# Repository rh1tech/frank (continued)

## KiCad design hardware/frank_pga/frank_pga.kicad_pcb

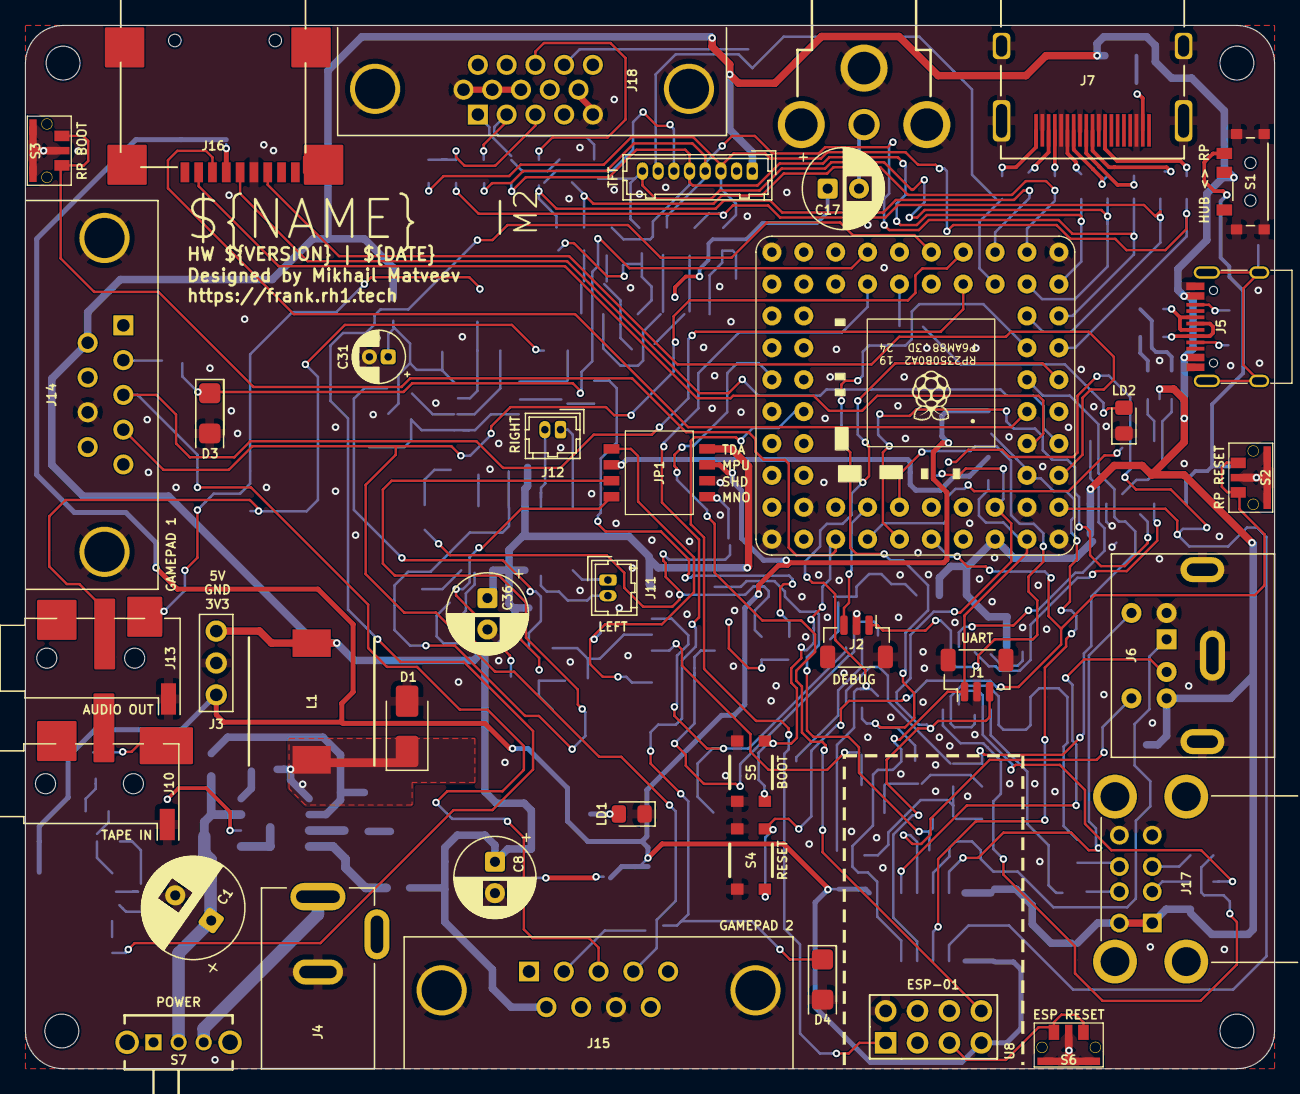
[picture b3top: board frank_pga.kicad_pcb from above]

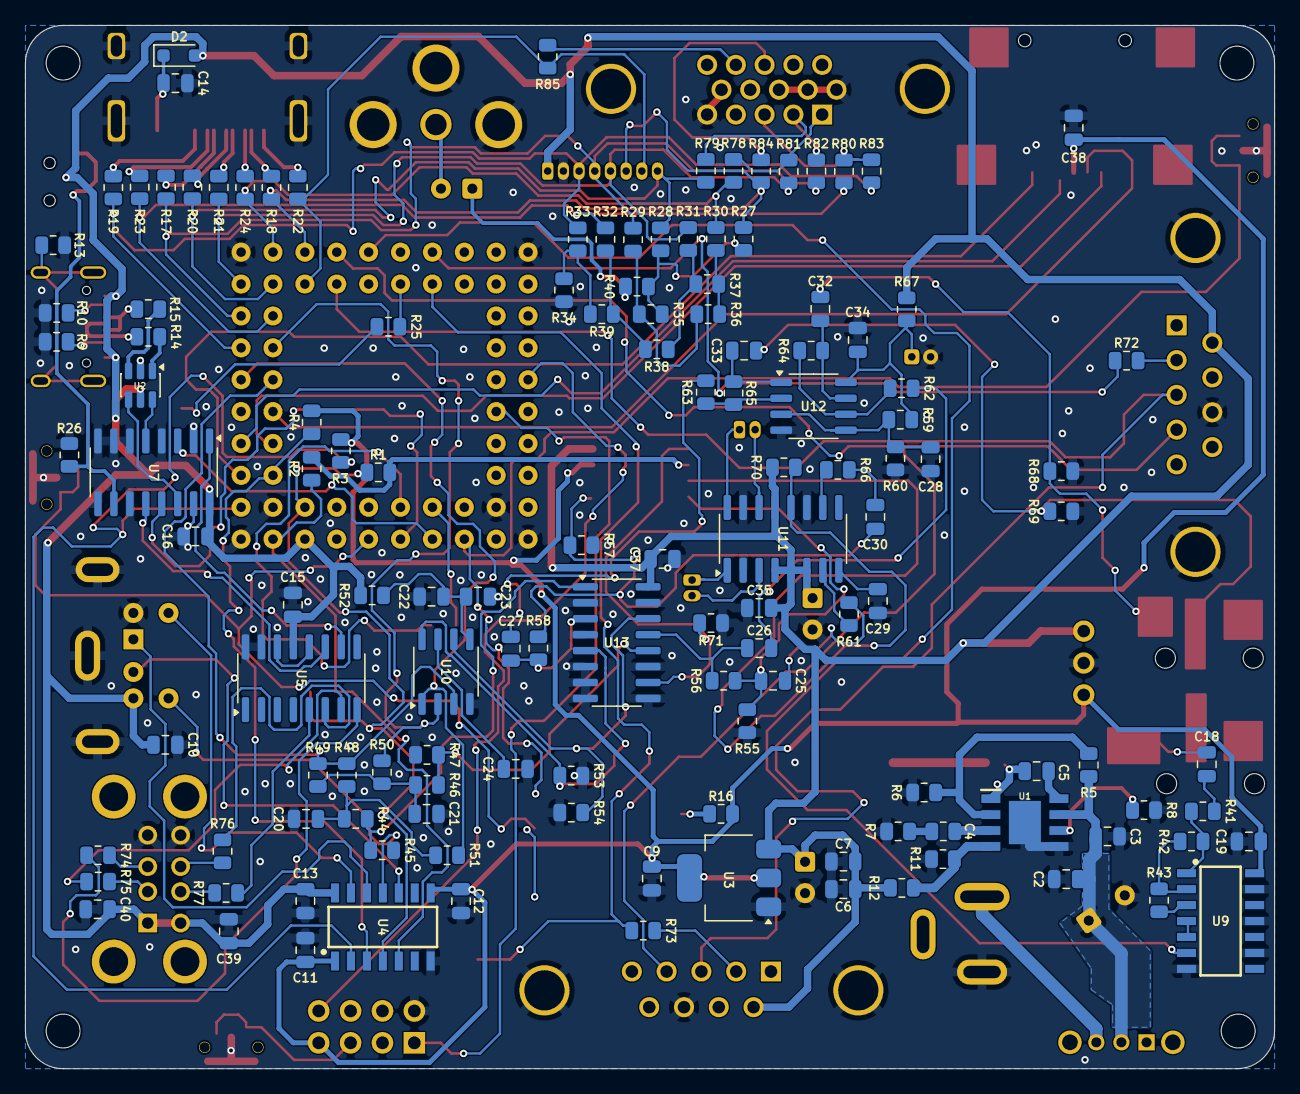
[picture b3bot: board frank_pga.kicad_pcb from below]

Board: 2 copper layers, 99.5 x 83.1 mm, 175 parts (132 on the bottom side), 137 nets.

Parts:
C1: 680u; C_Radial_D8.0mm_P3.50mm
C2, C7, C9, C22, C24, C26, C27, C28, C32, C33, C39, C40: 10u; C_0805_2012Metric
C3, C5, C6, C10, C11, C12, C13, C14, C16, C18, C19, C23, C29, C34, C37, C38: 100n; C_0805_2012Metric
C4: 150pF; R_0805_2012Metric
C8, C17: 220u; C_Radial_D6.3mm_P2.50mm
C15: 4.7u; C_0805_2012Metric
C20, C21: 47n; C_0805_2012Metric
C25, C30, C35: 1u; C_0805_2012Metric
C31: 10u; CP_Radial_D4.0mm_P1.50mm
C36: 100u; C_Radial_D6.3mm_P2.50mm
D1: 1N5822; D_SMA
D2: 1N5819WS; D_SOD-323
D3, D4: 3V3; D_MiniMELF
H1, H2, H3, H4: Hole 2.7mm; MountingHole_2.7mm
J1: UART; JST_SH_1x03_P1.00mm_Vertical
J2: DEBUG; JST_SH_1x03_P1.00mm_Vertical
J3: PWR; PinHeader_1x03_P2.54mm
J4: DC-005-5A-2.0; BarrelJack_DC-005
J5: USB4215-03-A; USB_C_Receptacle
J6: MDC-036; MiniDIN_6pin_Female
J7: HDMI-001 19PCBTP; HDMI_Female
J8: RCA-103; BarrelJack_RCJ-012
J9: Pin Header 1x08; JST_GH_1x08_P1.25mm
J10: PJ-320D; AudioJack_3.5mm_PJ320D_TapeIn
J11: PAM L; JST_GH_1x02_P1.25mm
J12: PAM R; JST_GH_1x02_P1.25mm
J13: PJ-320D; AudioJack_3.5mm_PJ320D_AudioOut
J14, J15: GP2; DSUB-9_Male_TopMount
J16: 104031-0811; MicroSD_SMD_Long
J17: SS-52100-004; USB_A_Stacked
J18: VGA; DSUB-15_Female
JP1: Config Switches; DIPSwitch_4pos_DS05
L1: 22uH; Inductor_CDRH104RNP
LD1: Green; LED_0805
LD2: Blue; LED_0805
R1, R2, R3, R4, R26, R44, R46, R56, R58, R59, R60, R61, R62, R63, R66, R70, R71: 10K; R_0805_2012Metric
R5, R7, R8, R42, R43: 100K; R_0805_2012Metric
R6: 24K; R_0805_2012Metric
R9, R10: 5.1K; R_0805_2012Metric
R11: 8.2K; R_0805_2012Metric
R12: 43K; R_0805_2012Metric
R13: 1M; R_0805_2012Metric
R14, R15, R74, R75, R76, R77: 22R; R_0805_2012Metric
R16, R25, R50, R51, R72, R73, R81, R82, R83: 1K; R_0805_2012Metric
R17, R18, R19, R20, R21, R22, R23, R24, R28, R29, R30, R31, R32, R33: 270R; R_0805_2012Metric
R27: 750R; R_0805_2012Metric
R34: 300R; R_0805_2012Metric
R35, R36, R37, R38, R39: 150R; R_0805_2012Metric
R40: 51R; R_0805_2012Metric
R41: 4.7K; R_0805_2012Metric
R45, R47, R48, R49, R55, R57: 2K; R_0805_2012Metric
R52, R67, R84, R85: 100R; R_0805_2012Metric
R53, R54: 470R; R_0805_2012Metric
R64, R65: 47K; R_0805_2012Metric
R68, R69: 20K; R_0805_2012Metric
R78, R79, R80: 330R; R_0805_2012Metric
S1: MSK12C02; Switch_Slide_MSK12C02
S2: RP Reset; Button_SMD_TS1234VW
S3: RP BOOT; Button_SMD_TS1234VW
S4: RP Reset; Button_SMD_3x4x2mm
S5: RP BOOT; Button_SMD_3x4x2mm
S6: ESP Reset; Button_SMD_TS1234VW
S7: SK12D07VG3NS; Switch_Slide_SK12D07VG3NS
U1: MP1584EN-LF-Z; SOIC-9_P1.27mm
U2: USBLC6-2SC6; SOT-23-6
U3: AMS1117 3.3; SOT-223-3_TabPin2
U4: TXS0104EDR; SOIC-14_P1.27mm
U5: MW7211A; SOP-16_P1.27mm
U6: Pimoroni PGA2350; PGA2350
U7, U13: 74HC4052D; SOP-16_P1.27mm
U8: ESP-01v090; ESP-01S
U9: CD4069UBM; SOIC-14_P1.27mm
U10: TDA1387T; SO-8
U11: PAM8403D; SOP-16_P1.27mm
U12: LM358; SO-8

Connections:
+3V3: C9.1, C11.1, C12.1, C19.1, C38.2, J3.1, J16.4 (VDD), JP1.4 (NO_2), R3.2, R4.2, R16.2, U3.2 (VO), U4.1 (VCCA), U4.8 (OE), U8.7 (VCC), U9.14 (VDD)
/AUDIOSW: JP1.1 (COM_1), R71.2, U13.10 (S0)
/Audio Multiplexer/AMP_IN_L: C26.1, R56.1, U13.13 (1Z)
/Audio Multiplexer/AMP_IN_R: C27.1, R58.1, U13.3 (2Z)
/Audio Multiplexer/PWM_OUT_L: R46.2, R47.1, U13.12 (1Y0)
/Audio Multiplexer/PWM_OUT_R: R44.2, R45.1, U13.1 (2Y0)
/Audio Multiplexer/TDA_L: R54.2, U10.6 (A_LEFT), U13.14 (1Y1)
/Audio Multiplexer/TDA_R: R53.1, U10.8 (A_RIGHT), U13.5 (2Y1)
/Audio/AMP_OUTL: C32.2, J13.T, R68.2
/Audio/AMP_OUTR: C33.2, J13.R, R69.2
/Audio/AMP_PAM_OUTL_M: J11.2, U11.3 (-OUTL)
/Audio/AMP_PAM_OUTL_P: J11.1, U11.1 (+OUT_L)
/Audio/AMP_PAM_OUTR_M: J12.2, U11.14 (-OUT_R)
/Audio/AMP_PAM_OUTR_P: J12.1, U11.16 (+OUT_R)
/Audio/MONO_L: C25.1, JP1.7 (COM_4), R55.1, R56.2
/Audio/MONO_R: C30.1, JP1.8 (NO_4), R57.1, R58.2
/Audio/SHND: JP1.5 (COM_3), R70.2, U11.12 (SHND)
/Composite/CVBS: C17.2, J8.1
/ESP Reset/RST: S6.1, U8.5 (RST)
/MSPUP3V3: JP1.3 (COM_2), R1.2, R2.2
/PBOOTSEL: S3.1, S5.1, S5.3, U6.51 (BOOTSEL)
/PGPIO0: J1.1, R1.1, U4.4 (A3), U6.61 (GP0)
/PGPIO1: J1.3, R2.1, U4.5 (A4), U6.62 (GP1)
/PGPIO2: R3.1, U4.2 (A1), U6.2 (GP2)
/PGPIO3: R4.1, U4.3 (A2), U6.3 (GP3)
/PGPIO4: J16.7 (DAT0), U6.4 (GP4)
/PGPIO5: J16.2 (DAT3/CD), U6.5 (GP5)
/PGPIO6: J16.5 (CLK), U6.6 (GP6)
/PGPIO7: J16.3 (CMD), U6.7 (GP7)
/PGPIO9: R48.1, R49.1, U6.9 (GP9), U10.3 (DATA)
/PGPIO10: R51.2, U6.10 (GP10), U10.1 (SCLK)
/PGPIO11: R50.2, U6.11 (GP11), U10.2 (LRCK)
/PGPIO12: J9.3, R19.2, R33.1, R83.1, U6.12 (GP12)
/PGPIO13: R23.2, R32.1, R80.1, U6.13 (GP13)
/PGPIO14: J9.4, R17.2, R29.1, R82.1, U6.14 (GP14)
/PGPIO15: J9.8, R20.2, R28.1, R79.1, U6.15 (GP15)
/PGPIO16: J9.5, R21.2, R31.1, R81.1, U6.16 (GP16)
/PGPIO17: R24.2, R30.1, R78.1, U6.17 (GP17)
/PGPIO18: J9.6, R18.2, R27.1, R84.2, U6.19 (GP18)
/PGPIO19: J9.7, R22.2, R85.2, U6.20 (GP19)
/PGPIO20: J14.4, J15.4, U6.21 (GP20)
/PGPIO21: J14.3, J15.3, U6.22 (GP21)
/PGPIO22: U6.23 (GP22), U9.6 (I=*C)
/PGPIO26: D3.1 (K), R72.1, U6.27 (GP26)
/PGPIO27: D4.1 (K), R73.1, U6.28 (GP27)
/PGPIO38: U6.40 (GP38), U8.8 (URXD)
/PGPIO39: U6.41 (GP39), U8.1 (UTXD)
/PRUN: S2.1, S4.1, S4.3, U6.56 (RUN)
/PS2/KB_CLK_5V: J6.5, U4.13 (B1)
/PS2/KB_DATA_5V: J6.1, U4.12 (B2)
/PS2/MS_CLK_5V: J6.6, U4.11 (B3)
/PS2/MS_DATA_5V: J6.2, U4.10 (B4)
/PSWCLK: J2.3, U6.55 (SWCLK)
/PSWDIO: J2.1, U6.52 (SWDIO)
/Power/D+: J5.6 (DP1), J5.8 (DP2), R15.2
/Power/D-: J5.5 (DN2), J5.7 (DN1), R14.2
/Power/DM: U2.6 (I/O1), U7.5 (2Y1)
/Power/DP: U2.4 (I/O2), U7.14 (1Y1)
/Power/VBUS_IN: C1.1, C2.1, C3.1, R5.2, S7.2, U1.7 (VIN)
/TC_DM: U6.53 (USB_DM), U7.3 (2Z)
/TC_DP: U6.54 (USB_DP), U7.13 (1Z)
/Tape In/TAPE: C18.2, J10.T
/UM_SW: R26.2, S1.3, U7.10 (S0)
/USB Hub/DM1: R75.1, U5.7 (DM3)
/USB Hub/DM2: R77.1, U5.5 (DM2)
/USB Hub/DM_IN: U5.10 (DMU), U7.1 (2Y0)
/USB Hub/DP1: R74.1, U5.8 (DP3)
/USB Hub/DP2: R76.1, U5.6 (DP2)
/USB Hub/DP_IN: U5.11 (DPU), U7.12 (1Y0)
GND: C1.2, C2.2, C3.2, C6.1, C7.2, C8.2, C9.2, C10.2, C11.2, C12.2, C13.2, C14.2, C15.2, C16.1, C19.2, C20.2, C21.2, C22.2, C23.2, C24.2, C28.1, C29.2, C31.2, C34.1, C35.2, C36.2, C37.1, C38.1, C39.2, C40.2, D1.2 (A), D3.2 (A), D4.2 (A), J1.2, J2.2, J3.2, J4.2, J5.1 (GND), J5.12 (GND), J6.3, J7.2 (G_D2), J7.5 (G_D1), J7.8 (G_D0), J7.11 (G_CLK), J7.17 (G_DDC/CEC), J7.20 (SHIELD1), J7.21 (SHIELD2), J7.22 (SHIELD3), J7.23 (SHIELD4), J8.2, J9.2, J10.S, J13.S, J14.8, J15.8, J16.6 (VSS), J17.4 (GND1), J17.8 (GND2), J18.0, J18.5, J18.6, J18.7, J18.8, J18.10, JP1.6 (NO_3), LD1.1 (K), LD2.1 (K), R6.2, R7.2, R8.2, R9.1, R10.1, R11.1, R13.1, R26.1, R34.1, R45.2, R47.2, R53.2, R54.1, R55.2, R57.2, R60.1, R68.1, R69.1, R71.1, S1.4_1 (GND), S1.4_2 (GND), S1.4_3 (GND), S1.4_4 (GND), S2.2, S2.3 (GND), S3.2, S3.3 (GND), S4.2, S4.4, S5.2, S5.4, S6.2, S6.3 (GND), U1.5 (GND), U1.9 (EP), U2.2 (GND), U3.1 (GND), U4.7 (GND), U5.15 (GND), U5.16 (GND), U6.1 (GND), U6.18 (GND), U6.33 (GND), U6.48 (GND), U7.2 (2Y2), U7.4 (2Y3), U7.6 (~E), U7.7 (VEE), U7.8 (GND), U7.9 (S1), U7.11 (1Y3), U7.15 (1Y2), U8.2 (GND), U9.7 (VSS), U9.9 (D14), U9.11 (E), U9.13 (F), U10.4 (AGND), U11.2 (PGND), U11.11 (GND), U11.15 (PGND), U12.4 (V-), U13.2 (2Y2), U13.4 (2Y3), U13.6 (~E), U13.7 (VEE), U13.8 (GND), U13.9 (S1), U13.11 (1Y3), U13.15 (1Y2)
GP25: R25.2, U6.26 (GP25)
unnamed: C4.2, R7.1
unnamed: C17.1, R40.2
unnamed: C18.1, R41.2
unnamed: C20.1, R44.1, R48.2, R51.1
unnamed: C21.1, R46.1, R49.2, R50.1
unnamed: C25.2, R61.2
unnamed: C26.2, R62.2
unnamed: C27.2, R63.2
unnamed: C30.2, R66.2
unnamed: C32.1, R64.1, U12.7
unnamed: C33.1, R65.1, U12.1
unnamed: C5.2, D1.1 (K), L1.1, U1.1 (SW)
unnamed: C14.1, D2.1 (K), J7.18 (+5V)
unnamed: J4.1, S7.3
unnamed: J5.4 (CC1), R9.2
unnamed: J5.10 (CC2), R10.2
unnamed: J5.13 (SHIELD), R13.2
unnamed: J7.12 (CLKN), R19.1
unnamed: J7.10 (CLKP), R23.1
unnamed: J7.9 (D0N), R17.1
unnamed: J7.7 (D0P), R20.1
unnamed: J7.6 (D1N), R21.1
unnamed: J7.4 (D1P), R24.1
unnamed: J7.3 (D2N), R18.1
unnamed: J7.1 (D2P), R22.1
unnamed: J14.2, R72.2
unnamed: J15.2, R73.2
unnamed: J17.3 (D1+), R74.2
unnamed: J17.2 (D1-), R75.2
unnamed: J17.7 (D2+), R76.2
unnamed: J17.6 (D2-), R77.2
unnamed: J18.1, R78.2, R81.2
unnamed: J18.2, R79.2, R82.2
unnamed: J18.3, R80.2, R83.2
unnamed: J18.13, R84.1
unnamed: J18.14, R85.1
unnamed: LD1.2 (A), R16.1
unnamed: LD2.2 (A), R25.1
unnamed: R14.1, U2.1 (I/O1)
unnamed: R15.1, U2.3 (I/O2)
unnamed: R27.2, R28.2, R35.2, R40.1
unnamed: R29.2, R35.1, R36.2
unnamed: R30.2, R36.1, R37.2
unnamed: R31.2, R37.1, R38.2
unnamed: R32.2, R38.1, R39.2
unnamed: R33.2, R34.2, R39.1
unnamed: C5.1, U1.8 (BST)
unnamed: C4.1, U1.3 (COMP)
unnamed: R5.1, R6.1, U1.2 (EN)
unnamed: R11.2, R12.2, U1.4 (FB)
unnamed: R8.1, U1.6 (FREQ)
unnamed: U5.12 (VD33), U5.14 (VD3)
unnamed: R41.1, R42.2, U9.1 (A)
unnamed: R43.1, U9.3 (B)
unnamed: U9.4 (H=*B), U9.5 (C)
unnamed: R42.1, R43.2, U9.2 (G-*A)
unnamed: C24.1, U10.7 (FLT)
unnamed: C22.1, C23.1, R52.1, U10.5 (VA)
unnamed: R61.1, U11.7 (INL)
unnamed: R66.1, U11.10 (INR)
unnamed: C29.1, U11.8 (VREF)
unnamed: C28.2, R59.1, R60.2, U12.3 (+), U12.5 (+)
unnamed: R63.1, R65.2, U12.2 (-)
unnamed: R62.1, R64.2, U12.6 (-)
unnamed: C31.1, C34.2, R59.2, R67.2, U12.8 (V+)
VBUS: C6.2, C7.1, C8.1, C10.1, C13.1, C15.1, C16.2, C35.1, C36.1, C37.2, C39.1, C40.1, D2.2 (A), J3.3, J5.2 (VBUS), J5.11 (VBUS), J6.4, J9.1, J14.6, J15.6, J17.1 (VBUS1), J17.5 (VBUS2), JP1.2 (NO_1), L1.2, R12.1, R52.2, R67.1, R70.1, S1.2, U2.5 (VBUS), U3.3 (VI), U4.14 (VCCB), U5.13 (VDD5), U6.60 (VBUS), U7.16 (VCC), U11.4 (PVDD), U11.5 (MUTE), U11.6 (VDD), U11.13 (PVDD), U13.16 (VCC)

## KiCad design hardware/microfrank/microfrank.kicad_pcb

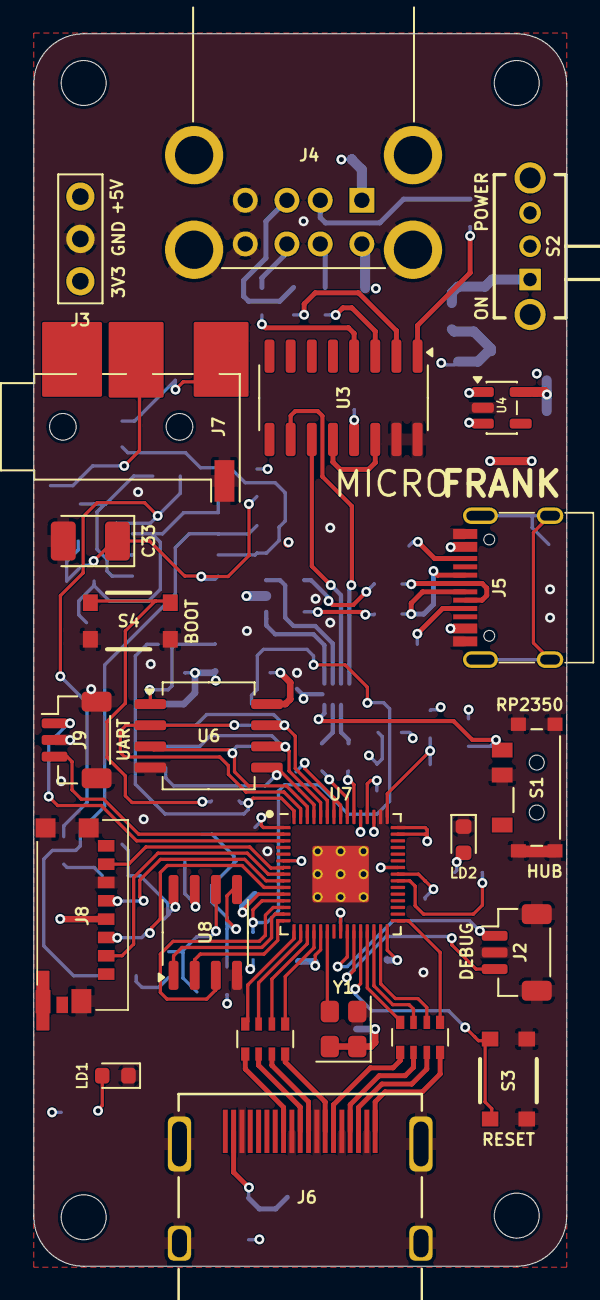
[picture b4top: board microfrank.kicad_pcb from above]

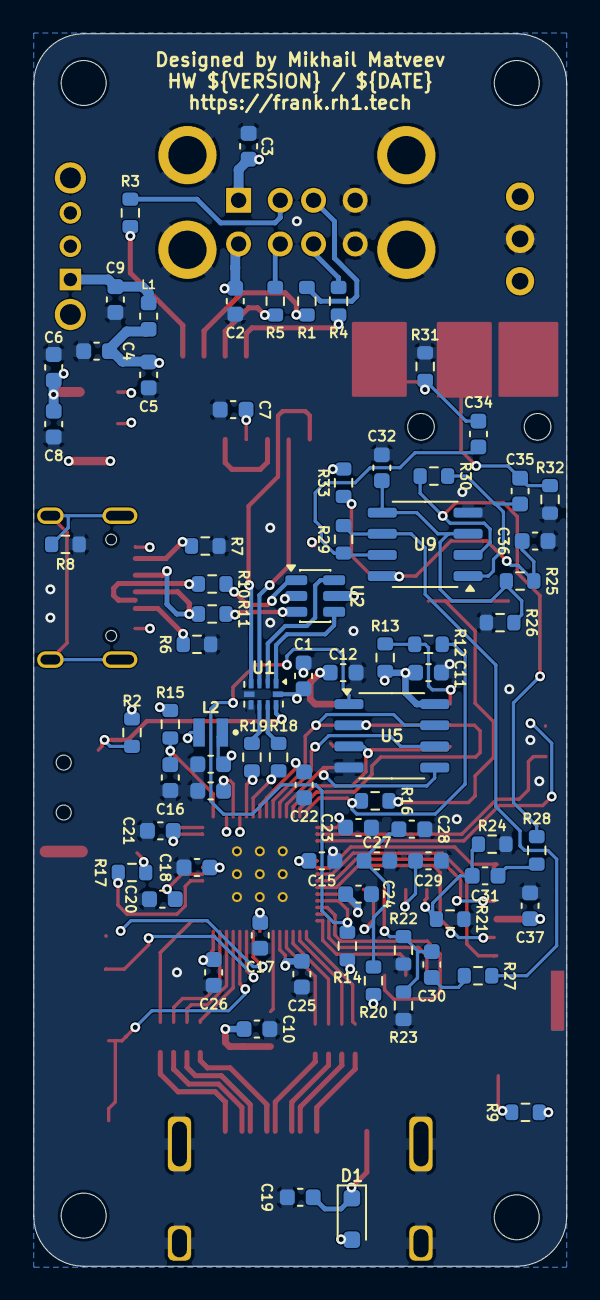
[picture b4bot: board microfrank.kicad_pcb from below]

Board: 4 copper layers, 32.0 x 74.0 mm, 103 parts (76 on the bottom side), 89 nets.

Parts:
C1, C5, C6, C9, C10, C11, C12, C15, C18, C19, C20, C21, C22, C23, C24, C25, C26, C28, C36, C37: 100n; C_0603_1608Metric
C2, C3, C4, C8, C27, C29, C30, C31, C32, C34, C35: 10u; C_0603_1608Metric
C7, C13, C14, C16, C17: 4.7u; C_0603_1608Metric
C33: 10u; C_3528_Tantalum
D1: 1N5819WS; D_SOD-323
H1, H2, H3, H4: Hole 2.7mm; MountingHole_2.7mm
J2, J9: DEBUG; JST_SH_1x03_P1.00mm_Vertical
J3: PWR; PinHeader_1x03_P2.54mm
J4: SS-52100-004; USB_A_Stacked
J5: USB4215-03-A; USB_C_Receptacle
J6: HDMI-001 19PCBTP; HDMI_Female
J7: PJ-320D; AudioJack_3.5mm_PJ320D
J8: 0475710001; MicroSD_SMD_Short
L1: 330R; L_0603_1608Metric
L2: 3.3u; L_2016_Polarized
LD1: Green; LED_0603_1608Metric
LD2: Blue; LED_0603_1608Metric
R1, R3, R4, R5, R10, R11: 22R; R_0603_1608Metric
R2, R13, R14, R23, R24, R25, R26, R27, R28: 10K; R_0603_1608Metric
R6, R7: 5.1K; R_0603_1608Metric
R8: 1M; R_0603_1608Metric
R9, R16, R17: 1K; R_0603_1608Metric
R12: 0R; R_0603_1608Metric
R15: 33R; R_0603_1608Metric
R18, R19: 27R; R_0603_1608Metric
R20, R33: 100R; R_0603_1608Metric
R21, R22: 470R; R_0603_1608Metric
R29, R30: 47K; R_0603_1608Metric
R31, R32: 20K; R_0603_1608Metric
RN1, RN2: 270R; R_Array_4x0603
S1: MSK12C02; Switch_Slide_MSK12C02
S2: SK12D07VG3NS; Switch_Slide_SK12D07VG3NS
S3, S4: Button; Button_SMD_3x4x2mm
U1: TS3USB221RSER; UQFN-10
U2: USBLC6-2SC6; SOT-23-6
U3: MW7211A; SOP-16_P1.27mm
U4: ME6211C33M5; SOT-23-5
U5: ESP-PSRAM64H; SO-8
U6: W25Q128JVS; SOIC-8
U7: RP2350; QFN-60_RP2350A
U8: TDA1387T; SO-8
U9: LM358; SO-8
Y1: ASE-12MHz; Oscillator_SMD_Abracon_ASE-4Pin_3.2x2.5mm

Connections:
+1V1: C14.1, C15.1, C17.1, C18.1, L2.1, U7.6 (DVDD), U7.23 (DVDD), U7.39 (DVDD), U7.50 (VREG_FB)
+3V3: C1.2, C6.1, C8.1, C10.1, C11.1, C12.1, C13.1, C20.1, C21.1, C22.1, C23.1, C24.1, C25.1, C26.1, C37.2, J3.1, J8.P4 (VDD), R2.1, R9.2, R13.1, R14.2, R15.1, U1.10 (VCC), U4.5 (V_{OUT}), U5.8 (VCC), U6.8 (VCC), U7.1 (IOVDD), U7.11 (IOVDD), U7.20 (IOVDD), U7.30 (IOVDD), U7.38 (IOVDD), U7.44 (ADC_AVDD), U7.45 (IOVDD), U7.49 (VREG_VIN), U7.53 (USB_OTP_VDD), U7.54 (QSPI_IOVDD), Y1.1 (EN), Y1.4 (Vdd)
/Audio/AMP_OUTL: C34.2, J7.T, R31.2
/Audio/AMP_OUTR: C35.2, J7.R, R32.2
/Audio/TDA_DATA: U7.13 (GPIO9), U8.3 (DATA)
/Audio/TDA_L: C30.1, R22.2, R23.1, U8.6 (A_LEFT)
/Audio/TDA_LRCK: U7.15 (GPIO11), U8.2 (LRCK)
/Audio/TDA_R: C31.1, R21.1, R24.1, U8.8 (A_RIGHT)
/Audio/TDA_SCLK: U7.14 (GPIO10), U8.1 (SCLK)
/HDMI/CLKN: RN1.4 (R4.1), U7.16 (GPIO12)
/HDMI/CLKP: RN1.3 (R3.1), U7.17 (GPIO13)
/HDMI/D0N: RN1.2 (R2.1), U7.18 (GPIO14)
/HDMI/D0P: RN1.1 (R1.1), U7.19 (GPIO15)
/HDMI/D1N: RN2.4 (R4.1), U7.27 (GPIO16)
/HDMI/D1P: RN2.3 (R3.1), U7.28 (GPIO17)
/HDMI/D2N: RN2.2 (R2.1), U7.29 (GPIO18)
/HDMI/D2P: RN2.1 (R1.1), U7.31 (GPIO19)
/Micro SD/CDDAT3: J8.P2 (CD/DAT3), U7.8 (GPIO5)
/Micro SD/CLK: J8.P5 (CLK), U7.9 (GPIO6)
/Micro SD/CMD: J8.P3 (CMD), U7.10 (GPIO7)
/Micro SD/DAT0: J8.P7 (DAT0), U7.7 (GPIO4)
/Power/D1+: U1.1 (1D+), U2.4 (I/O2)
/Power/D1-: U1.2 (1D-), U2.6 (I/O1)
/Power/D2+: U1.3 (2D+), U3.11 (DPU)
/Power/D2-: U1.4 (2D-), U3.10 (DMU)
/Power/D+: R18.1, U1.8 (D+)
/Power/D-: R19.1, U1.7 (D-)
/Power/DS1+: R1.1, U3.2 (DP0)
/Power/DS1-: R3.1, U3.1 (DM0)
/Power/DS2+: R4.1, U3.4 (DP1)
/Power/DS2-: R5.1, U3.3 (DM1)
/Power/S: R2.2, S1.3, U1.9 (S)
/Power/VBUS_IN: J5.2 (VBUS), J5.11 (VBUS), S2.2
/RP2350A/FLASH_SS: R12.2, R13.2, U6.1 (~CS)
/RP2350A/GPIO0: J9.1, U7.2 (GPIO0)
/RP2350A/GPIO1: J9.3, U7.3 (GPIO1)
/RP2350A/GPIO8: R14.1, U5.1 (~CE), U7.12 (GPIO8)
/RP2350A/QSPI_SCLK: U5.6 (SCLK), U6.6 (CLK), U7.56 (QSPI_SCLK)
/RP2350A/QSPI_SD0: U5.5 (SI/SIO), U6.5 (DI(IO0)), U7.57 (QSPI_SD0)
/RP2350A/QSPI_SD1: U5.2 (SO/SIO), U6.2 (DO(IO1)), U7.59 (QSPI_SD1)
/RP2350A/QSPI_SD2: U5.3 (SIO2), U6.3 (IO2), U7.58 (QSPI_SD2)
/RP2350A/QSPI_SD3: U5.7 (SIO3), U6.7 (IO3), U7.55 (QSPI_SD3)
/RP2350A/QSPI_SS: R12.1, R16.1, U7.60 (QSPI_SS)
/RP2350A/SWCLK: J2.3, U7.24 (SWCLK)
/RP2350A/SWD: J2.1, U7.25 (SWD)
/RP2350A/VREG_AVDD: C16.1, R15.2, U7.46 (VREG_AVDD)
/RP2350A/VREG_LX: L2.2, U7.48 (VREG_LX)
/RP2350A/XIN: U7.21 (XIN), Y1.3 (OUT)
/RP2350A/~USB_BOOT: R16.2, S4.2, S4.4
/RP Reset/C1: S3.2, S3.4, U7.26 (RUN)
GND: C1.1, C2.2, C3.2, C4.1, C5.1, C6.2, C7.2, C8.2, C9.2, C10.2, C11.2, C12.2, C13.2, C14.2, C15.2, C16.2, C17.2, C18.2, C19.2, C20.2, C21.2, C22.2, C23.2, C24.2, C25.2, C26.2, C27.2, C28.2, C29.2, C32.1, C33.2, C36.1, C37.1, J2.2, J3.2, J4.4 (GND1), J4.8 (GND2), J4.SH (Shield), J5.1 (GND), J5.12 (GND), J6.2 (G_D2), J6.5 (G_D1), J6.8 (G_D0), J6.11 (G_CLK), J6.17 (G_DDC/CEC), J6.20 (SHIELD1), J6.21 (SHIELD2), J6.22 (SHIELD3), J6.23 (SHIELD4), J7.S, J8.P6 (VSS), J8.SH (GND_2), J9.2, LD1.1 (K), LD2.1 (K), R6.1, R7.1, R8.2, R21.2, R22.1, R23.2, R24.2, R26.1, R31.1, R32.1, S1.2, S1.4 (GND_4), S3.1, S3.3, S4.1, S4.3, U1.5 (GND), U1.6 (~OE), U2.2 (GND), U3.15 (GND), U3.16 (GND), U4.2 (V_{SS}), U5.4 (VSS), U6.4 (GND), U7.47 (VREG_PGND), U7.61 (GND), U8.4 (AGND), U9.4 (V-), Y1.2 (GND)
GPIO25: R17.2, U7.37 (GPIO25)
unnamed: C9.1, L1.2, S2.1
unnamed: C30.2, R27.2
unnamed: C31.2, R28.2
unnamed: C34.1, R29.1, U9.7
unnamed: C35.1, R30.1, U9.1
unnamed: C19.1, D1.1 (K), J6.18 (+5V)
unnamed: J4.3 (D1+), R1.2
unnamed: J4.2 (D1-), R3.2
unnamed: J4.7 (D2+), R4.2
unnamed: J4.6 (D2-), R5.2
unnamed: J5.4 (CC1), R6.2
unnamed: J5.10 (CC2), R7.2
unnamed: J5.5 (DN2), J5.7 (DN1), R10.2
unnamed: J5.6 (DP1), J5.8 (DP2), R11.2
unnamed: J5.13 (SHIELD), R8.1
unnamed: J6.12 (CLKN), RN1.5 (R4.2)
unnamed: J6.10 (CLKP), RN1.6 (R3.2)
unnamed: J6.9 (D0N), RN1.7 (R2.2)
unnamed: J6.7 (D0P), RN1.8 (R1.2)
unnamed: J6.6 (D1N), RN2.5 (R4.2)
unnamed: J6.4 (D1P), RN2.6 (R3.2)
unnamed: J6.3 (D2N), RN2.7 (R2.2)
unnamed: J6.1 (D2P), RN2.8 (R1.2)
unnamed: LD1.2 (A), R9.1
unnamed: LD2.2 (A), R17.1
unnamed: R10.1, U2.1 (I/O1)
unnamed: R11.1, U2.3 (I/O2)
unnamed: U3.12 (VD33), U3.14 (VD3)
unnamed: R19.2, U7.51 (USB_DM)
unnamed: R18.2, U7.52 (USB_DP)
unnamed: C29.1, U8.7 (FLT)
unnamed: C27.1, C28.1, R20.1, U8.5 (VA)
unnamed: C32.2, R25.1, R26.2, U9.3 (+), U9.5 (+)
unnamed: R28.1, R30.2, U9.2 (-)
unnamed: R27.1, R29.2, U9.6 (-)
unnamed: C33.1, C36.2, R25.2, R33.2, U9.8 (V+)
VBUS: C2.1, C3.1, C4.2, C5.2, C7.1, D1.2 (A), J3.3, J4.1 (VBUS1), J4.5 (VBUS2), L1.1, R20.2, R33.1, U2.5 (VBUS), U3.13 (VDD5), U4.1 (V_{IN}), U4.3 (CE)

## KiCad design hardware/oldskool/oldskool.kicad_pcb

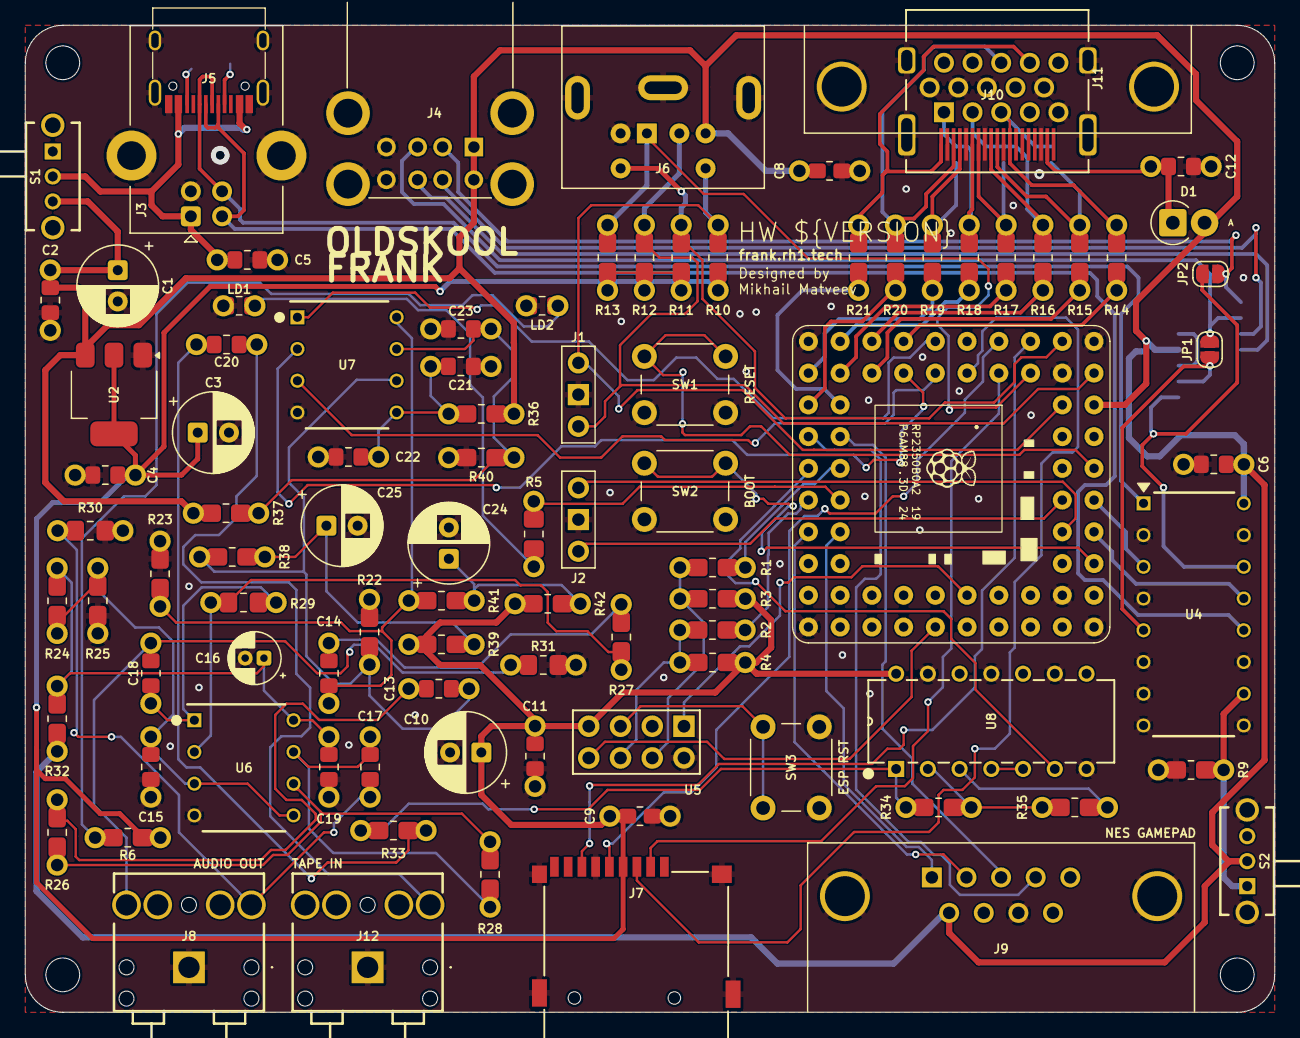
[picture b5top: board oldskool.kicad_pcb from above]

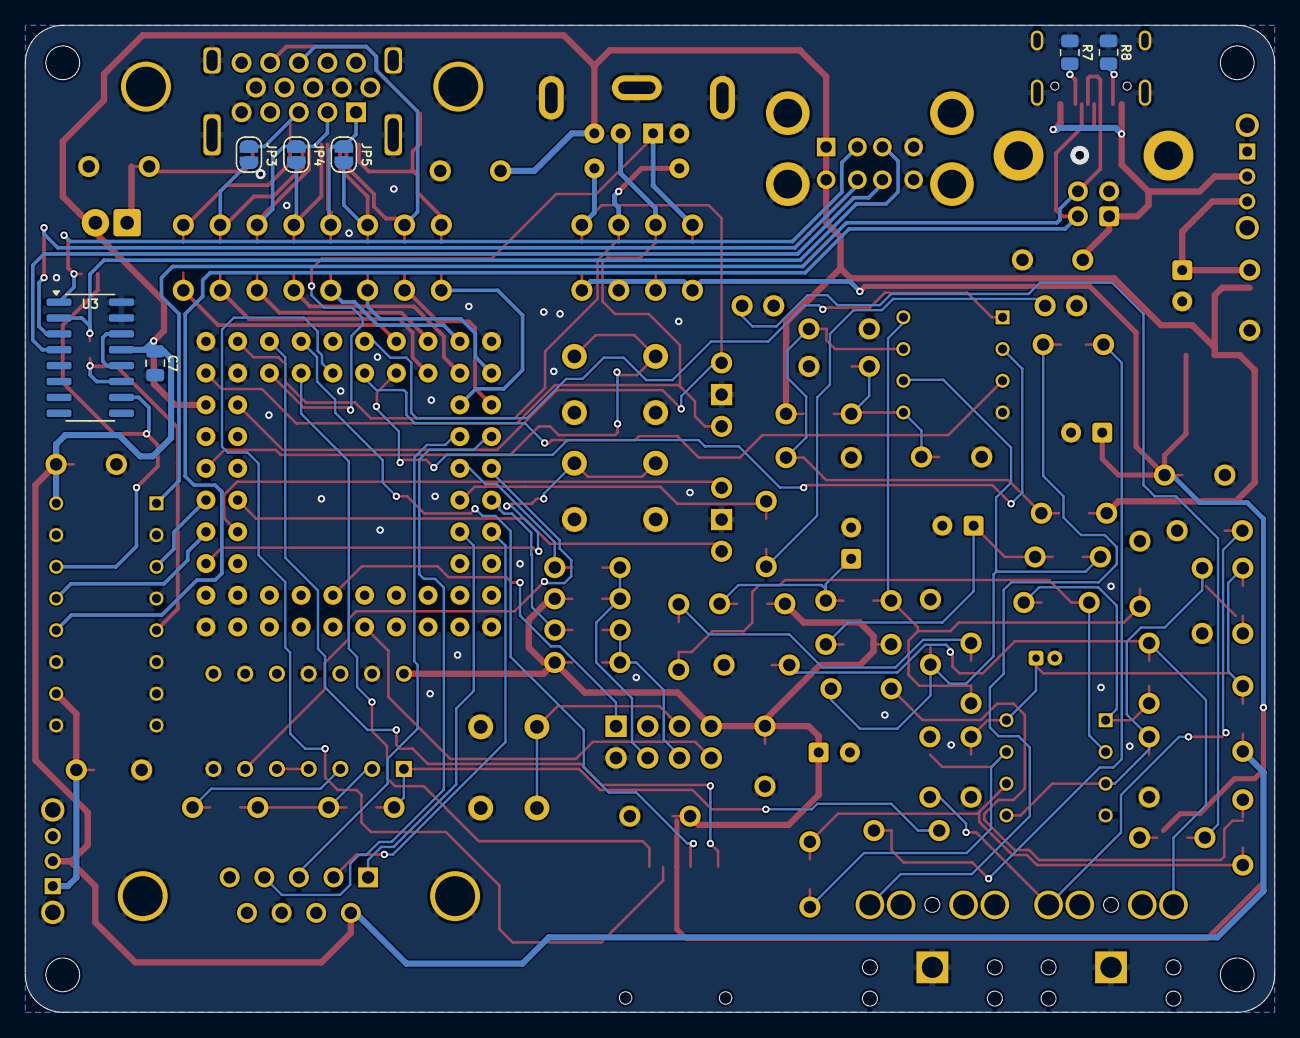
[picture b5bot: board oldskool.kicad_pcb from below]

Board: 2 copper layers, 100.0 x 79.0 mm, 104 parts (7 on the bottom side), 87 nets.

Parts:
C1, C3, C10, C24, C25: 100u; C_Radial_D6.3mm_P2.50mm
C2, C4, C6, C8, C9, C11, C12, C19, C20, C22: 100n; Combined_0805_CR
C5, C13, C14, C15, C17, C18, C21, C23: 10u; Combined_0805_CR
C7: 4.7u; C_0805_2012Metric
C16: 10u; CP_Radial_D4.0mm_P1.50mm
D1: 1N5819; D_SOD81_P2.54mm_Vertical_AnodeUp
H1, H2, H3, H4: Hole 2.7mm; MountingHole_2.7mm
J1: UART; PinSocket_1x03_P2.54mm_Vertical
J2: Debug; PinSocket_1x03_P2.54mm_Vertical
J3: USB_B; USB_B_Horizontal
J4: SS-52100-004; USB_A_Stacked
J5: USB4215-03-A; USB_C_Receptacle
J6: MDC-036; MiniDIN_6pin_Female
J7: 104031-0811; MicroSD_SMD_Long
J8: SJ1-3525N Green; AudioJack_3.5mm_SJ1-3525N_Green
J9: D-SUB 9 Male; DSUB-9_Male_TopMount
J10: HDMI-001 19PCBTP; HDMI_Female
J11: D-SUB 15 Female; DSUB-15_Female
J12: SJ1-3525N Red; AudioJack_3.5mm_SJ1-3525N_Red
JP1, JP2, JP3, JP4, JP5: Jumper (Solder); SolderJumper_2Pin
LD1: Blue; Combined_0805_LED
LD2: Green; Combined_0805_LED
R1, R2, R5, R6, R10, R11, R12, R13: 1K; Combined_0805_RE
R3, R4, R9, R24, R25, R26, R27, R40: 10K; Combined_0805_RE
R7, R8: 5.1K; R_0805_2012Metric
R14, R15, R16, R17, R18, R19, R20, R21: 220R; Combined_0805_RE
R22, R23: 2.2K; Combined_0805_RE
R28, R29: 47K; Combined_0805_RE
R30, R31: 20K; Combined_0805_RE
R32, R36, R39, R42: 100R; Combined_0805_RE
R33: 4.7K; Combined_0805_RE
R34, R35: 100K; Combined_0805_RE
R37: 51K; Combined_0805_RE
R38, R41: 470R; Combined_0805_RE
S1, S2: SK12D07VG3NS; Switch_Slide_SK12D07VG3NS
SW1: Reset; SW_PUSH_6mm_H5mm
SW2: Boot; SW_PUSH_6mm_H5mm
SW3: ESP01 Reset; SW_PUSH_6mm_H5mm
U1: Pimoroni PGA2350; PGA2350
U2: AMS1117-3.3; SOT-223-3_TabPin2
U3: MW7211A; SOP-16_3.9x9.9mm_P1.27mm
U4: 74HC4052; 74HC4052N
U5: ESP-01v090; ESP-01S
U6: LM358; DIP-8_W7.94mm_P2.54mm
U7: TDA1545A; DIP-8_W7.94mm_P2.54mm
U8: CD4069UBE

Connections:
+3V3: C3.1, C4.2, C9.2, C10.1, C11.2, J7.4 (VDD), R3.2, R4.2, R6.2, R10.2, R11.2, R12.2, R13.2, R39.1, R42.1, U2.2 (VO), U5.7 (VCC), U8.14 (VDD)
/Audio/AMP_OUTL: C17.2, J8.2 (TIP), R30.2
/Audio/AMP_OUTR: C18.2, J8.3 (RING), R31.2
/Audio/TDA_L: C13.1, R22.1, R38.2, U7.6 (IOL)
/Audio/TDA_R: C14.1, R23.1, R41.1, U7.8 (IOR)
/CDDAT3/GP5: J7.2 (DAT3/CD), U1.5 (GP5)
/CLKN/GP12: R14.2, U1.12 (GP12)
/CLKP/GP13: R15.2, U1.13 (GP13)
/CLK/GP6: J7.5 (CLK), U1.6 (GP6)
/CMD/GP7: J7.3 (CMD), U1.7 (GP7)
/D0N/GP14: R16.2, U1.14 (GP14)
/D0P/GP15: R17.2, U1.15 (GP15)
/D1N/GP16: R18.2, U1.16 (GP16)
/D1P/GP17: R19.2, U1.17 (GP17)
/D2N/GP18: R20.2, U1.19 (GP18)
/D2P/GP19: R21.2, U1.20 (GP19)
/DAT0/GP4: J7.7 (DAT0), U1.4 (GP4)
/DATA1/GP26: J9.2, U1.27 (GP26)
/DATA2/GP27: J9.1, U1.28 (GP27)
/DM: U1.53 (USB_DM), U4.13 (1Z)
/DP: U1.54 (USB_DP), U4.3 (2Z)
/EGP0/GP24: R2.2, U1.25 (GP24)
/EGP2/GP23: R1.2, U1.24 (GP23)
/ESP01S/GPIO0: R2.1, R4.1, U5.6 (GPIO0)
/ESP01S/GPIO2: R1.1, R3.1, U5.4 (GPIO2)
/J3/GP21: J9.3, U1.22 (GP21)
/J4/GP20: J9.4, U1.21 (GP20)
/KB_CLK/GP2: J6.5, R11.1, U1.2 (GP2)
/KB_DATA/GP3: J6.1, R13.1, U1.3 (GP3)
/LOAD_IN/GP22: U1.23 (GP22), U8.6 (I=*C)
/MS_CLK/GP0: J1.1, J6.6, R10.1, U1.61 (GP0)
/MS_DATA/GP1: J1.3, J6.2, R12.1, U1.62 (GP1)
/PGA2350/BOOTSEL: SW2.1, U1.51 (BOOTSEL)
/PGA2350/RUN: SW1.1, U1.56 (RUN)
/PGA2350/SWCLK: J2.3, U1.55 (SWCLK)
/PGA2350/SWDIO: J2.1, U1.52 (SWDIO)
/RX/GP38: U1.40 (GP38), U5.8 (URXD)
/TDA_DATA/GP9: U1.9 (GP9), U7.3 (DATA)
/TDA_LRCK/GP11: U1.11 (GP11), U7.2 (WS)
/TDA_SCLK/GP10: U1.10 (GP10), U7.1 (BCK)
/TX/GP39: U1.41 (GP39), U5.1 (UTXD)
/Tape In/TAPE: C20.2, J12.2 (TIP)
/USB/DI+: J3.3 (D+), J5.6 (DP1), J5.8 (DP2), U4.1 (2Y0)
/USB/DI-: J3.2 (D-), J5.5 (DN2), J5.7 (DN1), U4.12 (1Y0)
/USB/DS+: JP1.1 (A), U3.11 (DPU), U4.5 (2Y1)
/USB/DS-: JP2.1 (A), U3.10 (DMU), U4.14 (1Y1)
/USB/DU1+: J4.3 (D1+), JP1.2 (B), U3.2 (DP0)
/USB/DU1-: J4.2 (D1-), JP2.2 (B), U3.1 (DM0)
/USB/DU2+: J4.7 (D2+), U3.4 (DP1)
/USB/DU2-: J4.6 (D2-), U3.3 (DM1)
/USB/VBUS_IN: C5.1, J3.1 (VBUS), J5.2 (VBUS), J5.11 (VBUS), S1.2
/Video Out/VGA_B: J10.12 (CLKN), J11.3, JP3.1 (A), R14.1
/Video Out/VGA_BH: J10.10 (CLKP), JP3.2 (B), R15.1
/Video Out/VGA_G: J10.9 (D0N), J11.2, JP4.1 (A), R16.1
/Video Out/VGA_GH: J10.7 (D0P), JP4.2 (B), R17.1
/Video Out/VGA_HS: J10.3 (D2N), J11.13, R20.1
/Video Out/VGA_R: J10.6 (D1N), J11.1, JP5.1 (A), R18.1
/Video Out/VGA_RH: J10.4 (D1P), JP5.2 (B), R19.1
/Video Out/VGA_VS: J10.1 (D2P), J11.14, R21.1
GND: C1.2, C2.1, C3.2, C4.1, C5.2, C6.1, C7.2, C8.2, C9.1, C10.2, C11.1, C12.2, C15.1, C16.2, C19.1, C21.2, C22.2, C23.1, C24.2, C25.2, J1.2, J2.2, J3.4 (GND), J3.SH (Shield), J4.4 (GND1), J4.8 (GND2), J4.SH (Shield), J5.1 (GND), J5.12 (GND), J5.13 (SHIELD), J6.3, J7.6 (VSS), J8.1 (SLEEVE), J9.8, J10.2 (G_D2), J10.5 (G_D1), J10.8 (G_D0), J10.11 (G_CLK), J10.17 (G_DDC/CEC), J10.20 (SHIELD1), J10.21 (SHIELD2), J10.22 (SHIELD3), J10.23 (SHIELD4), J11.0, J11.5, J11.6, J11.7, J11.8, J11.10, J12.1 (SLEEVE), LD1.1 (K), LD2.1 (K), R7.1, R8.1, R9.1, R22.2, R23.2, R25.1, R30.1, R31.1, R40.1, S2.4 (MH1), S2.5 (MH2), SW1.2, SW2.2, SW3.2, U1.1 (GND), U1.18 (GND), U1.33 (GND), U1.48 (GND), U2.1 (GND), U3.15 (GND), U3.16 (GND), U4.2 (2Y2), U4.4 (2Y3), U4.6 (~E), U4.7 (VEE), U4.8 (GND), U4.9 (S1), U4.11 (1Y3), U4.15 (1Y2), U5.2 (GND), U6.4 (V-), U7.4 (GND), U8.7 (VSS), U8.9 (D14), U8.11 (E), U8.13 (F)
GP25: R5.2, U1.26 (GP25)
unnamed: C13.2, R26.2
unnamed: C14.2, R27.2
unnamed: C17.1, R28.1, U6.7
unnamed: C18.1, R29.1, U6.1
unnamed: C20.1, R33.2
unnamed: C24.1, R41.2, R42.2
unnamed: C25.1, R38.1, R39.2
unnamed: C12.1, D1.1 (K), J10.18 (+5V)
unnamed: J5.4 (CC1), R7.2
unnamed: J5.10 (CC2), R8.2
unnamed: LD1.2 (A), R5.1
unnamed: LD2.2 (A), R6.1
unnamed: U3.12 (VD33), U3.14 (VD3)
unnamed: R9.2, S2.1, U4.10 (S0)
unnamed: SW3.1, U5.5 (RST)
unnamed: C15.2, R24.1, R25.2, U6.3 (+), U6.5 (+)
unnamed: R27.1, R29.2, U6.2 (-)
unnamed: R26.1, R28.2, U6.6 (-)
unnamed: C16.1, C19.2, R24.2, R32.2, U6.8 (V+)
unnamed: C23.2, R37.2, R40.2, U7.7 (IREF)
unnamed: C21.1, C22.1, R36.1, U7.5 (VDD)
unnamed: R33.1, R34.2, U8.1 (A)
unnamed: R35.1, U8.3 (B)
unnamed: U8.4 (H=*B), U8.5 (C)
unnamed: R34.1, R35.2, U8.2 (G-*A)
VBUS: C1.1, C2.2, C6.2, C7.1, C8.1, D1.2 (A), J4.1 (VBUS1), J4.5 (VBUS2), J6.4, J9.6, R32.1, R36.2, R37.1, S1.3, S2.2, U1.60 (VBUS), U2.3 (VI), U3.13 (VDD5), U4.16 (VCC)

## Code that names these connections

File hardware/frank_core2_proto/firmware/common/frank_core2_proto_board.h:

/*
 * FRANK Core 2 — dual-RP2350 test firmware
 *
 * Copyright (c) 2026 Mikhail Matveev <xtreme@rh1.tech>
 * https://github.com/rh1tech/frank
 * SPDX-License-Identifier: GPL-3.0-or-later
 */

/*
 * frank_core2_proto_board.h — GPIO map for the FRANK Core 2 board.
 *
 * Every assignment below was extracted from the KiCad netlist
 * (frank_core2.kicad_sch -> kicad-cli sch export netlist), so this file
 * is the single source of truth shared by the master and slave builds.
 *
 * U3 = RP2350B (master, QFN-80)   U6 = RP2350  (slave, QFN-60)
 *
 * The master carries all the user-facing peripherals: HDMI (J5), microSD
 * (J7), TDA1387 I2S DAC (U8), USB-C host/device (J8), WS2812B status LED
 * (LD1) and 8 MB PSRAM (U2) + 16 MB flash (U1).
 *
 * The slave carries its own 8 MB PSRAM (U5) + 16 MB flash (U4), a USB-C
 * port (J9), a blue status LED (LD2) and a UART header (J4). Everything
 * else it needs it gets over the inter-processor link.
 */
#ifndef FRANK_CORE2_BOARD_H
#define FRANK_CORE2_BOARD_H

/* =====================================================================
 * Inter-processor link
 *
 * Two independent 8-bit source-synchronous buses, each with its own
 * clock and VALID strobe, plus three single-wire control signals.
 *
 *   Bus A  master -> slave   M.GPIO20..27 -> S.GPIO1..8
 *                            M.GPIO28 (CLK, 33R R1) -> S.GPIO9
 *                            M.GPIO29 (VALID)       -> S.GPIO10
 *
 *   Bus B  slave -> master   S.GPIO11..18 -> M.GPIO30..37
 *                            S.GPIO19 (CLK, 33R R2) -> M.GPIO38
 *                            S.GPIO20 (VALID)       -> M.GPIO39
 *
 * Both buses share the same relative layout, which the PIO programs
 * rely on: CLK == DATA_BASE + 8, VALID == DATA_BASE + 9. That lets one
 * pair of PIO programs serve both directions on both chips with nothing
 * but a different pin base.
 *
 * Control signals (plain SIO, no PIO):
 *   FS      M.GPIO40 -> S.GPIO21   frame-sync / phase strobe (master out)
 *   DB_MS   M.GPIO41 -> S.GPIO22   doorbell, master -> slave
 *   DB_SM   M.GPIO42 <- S.GPIO23   doorbell, slave  -> master
 *
 * NOTE ON GPIO43: the schematic labels M.GPIO43 as "RUNA/SR" (slave
 * reset), but the net only reaches a 10K pull-up to +3V3 (R3) — it is
 * NOT wired to the slave's RUN pin (U6.26), which only sees reset
 * button S4. The firmware therefore cannot reset the slave in hardware;
 * both MCUs must be reset/flashed independently. See README.md.
 * ===================================================================== */

/* ---- Master side (RP2350B / U3) ---- */
#define M_LINK_A_DATA_BASE   20   /* GPIO20..27, master -> slave  */
#define M_LINK_A_CLK         28   /* == DATA_BASE + 8             */
#define M_LINK_A_VALID       29   /* == DATA_BASE + 9             */

#define M_LINK_B_DATA_BASE   30   /* GPIO30..37, slave -> master  */
#define M_LINK_B_CLK         38
#define M_LINK_B_VALID       39

#define M_LINK_FS            40   /* out */
#define M_LINK_DB_OUT        41   /* DB_MS, out */
#define M_LINK_DB_IN         42   /* DB_SM, in  */
#define M_LINK_SLAVE_RUN     43   /* pull-up only — not connected, see above */

/* ---- Slave side (RP2350 / U6) ---- */
#define S_LINK_A_DATA_BASE    1   /* GPIO1..8, master -> slave (RX) */
#define S_LINK_A_CLK          9
#define S_LINK_A_VALID       10

#define S_LINK_B_DATA_BASE   11   /* GPIO11..18, slave -> master (TX) */
#define S_LINK_B_CLK         19
#define S_LINK_B_VALID       20

#define S_LINK_FS            21   /* in  */
#define S_LINK_DB_IN         22   /* DB_MS, in  */
#define S_LINK_DB_OUT        23   /* DB_SM, out */

/* =====================================================================
 * Master peripherals
 * ===================================================================== */

/* HDMI (J5) via HSTX — clock pair first, N before P, matches Murmulator 2 */
#define HDMI_BASE_PIN        12
#define HDMI_PIN_CLKN        12
#define HDMI_PIN_CLKP        13
#define HDMI_PIN_D0N         14
#define HDMI_PIN_D0P         15
#define HDMI_PIN_D1N         16
#define HDMI_PIN_D1P         17
#define HDMI_PIN_D2N         18
#define HDMI_PIN_D2P         19

/* microSD (J7) on SPI0 — SDIO pin names from the schematic in comments */
#define SDCARD_PIN_SPI0_MISO  4   /* SD DAT0    */
#define SDCARD_PIN_SPI0_CS    5   /* SD DAT3/CD */
#define SDCARD_PIN_SPI0_SCK   6   /* SD CLK     */
#define SDCARD_PIN_SPI0_MOSI  7   /* SD CMD     */

/* TDA1387T I2S DAC (U8) */
#define I2S_DATA_PIN          9   /* U8.3 DATA */
#define I2S_CLOCK_PIN_BASE   10   /* U8.1 SCLK = 10, U8.2 LRCK = 11 */

/* WS2812B status LED (LD1) via 330R R11 */
#define M_LED_WS2812_PIN     46

/* 8 MB PSRAM (U2 ESP-PSRAM64H) chip select */
#define M_PSRAM_CS_PIN       47

/* Debug UART header J2: pin1 = GPIO0 (TX), pin2 = GND, pin3 = GPIO1 (RX) */
#define M_UART_ID            uart0
#define M_UART_TX_PIN         0
#define M_UART_RX_PIN         1

/* Spare / unrouted master GPIOs (available for probing) */
#define M_SPARE_GPIO_LIST    { 2, 3, 8, 44, 45 }

/* =====================================================================
 * Slave peripherals
 * ===================================================================== */

/* 8 MB PSRAM (U5 ESP-PSRAM64H) chip select */
#define S_PSRAM_CS_PIN        0

/* Blue status LED (LD2) via 1K R19 — active high */
#define S_LED_PIN            26

/* Debug UART header J4: pin1 = GPIO24 (TX), pin2 = GND, pin3 = GPIO25 (RX) */
#define S_UART_ID            uart1
#define S_UART_TX_PIN        24
#define S_UART_RX_PIN        25

/* Spare / unrouted slave GPIOs */
#define S_SPARE_GPIO_LIST    { 27, 28, 29 }

/* =====================================================================
 * Memory devices (identical part numbers on both sides)
 * ===================================================================== */
#define FRANK_FLASH_PART     "W25Q128JVPIQ"
#define FRANK_FLASH_BYTES    (16u * 1024u * 1024u)
#define FRANK_PSRAM_PART     "ESP-PSRAM64H"
#define FRANK_PSRAM_BYTES    (8u * 1024u * 1024u)

/* XIP windows: CS0 = flash, CS1 = PSRAM (psram_init maps it there).
 *
 * The 0x14000000 aliases bypass the XIP cache entirely. That matters for
 * the PSRAM presence and size probes: through the cached window a write
 * followed by a read of the same address is answered out of the 8 KiB
 * cache, so a missing chip looks present and an address that aliases
 * back onto offset 0 looks like it does not. Throughput measurements
 * deliberately use the cached window, because that is how real code
 * reaches these devices. */
#define FRANK_XIP_FLASH_BASE         0x10000000u
#define FRANK_XIP_PSRAM_BASE         0x11000000u
#define FRANK_XIP_FLASH_NOCACHE_BASE 0x14000000u
#define FRANK_XIP_PSRAM_NOCACHE_BASE 0x15000000u

#endif /* FRANK_CORE2_BOARD_H */
